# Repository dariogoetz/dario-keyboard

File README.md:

# Ergonomic Split and Unibody 42-key Keyboards

Split and unibody variants of an ergonomic (column staggered) 42-key keyboard inspired by the [Cantor](https://github.com/diepala/cantor) keyboard and designed using [ergogen](https://github.com/ergogen/ergogen).

It uses a firmware based on [keyberon](https://github.com/TeXitoi/keyberon).

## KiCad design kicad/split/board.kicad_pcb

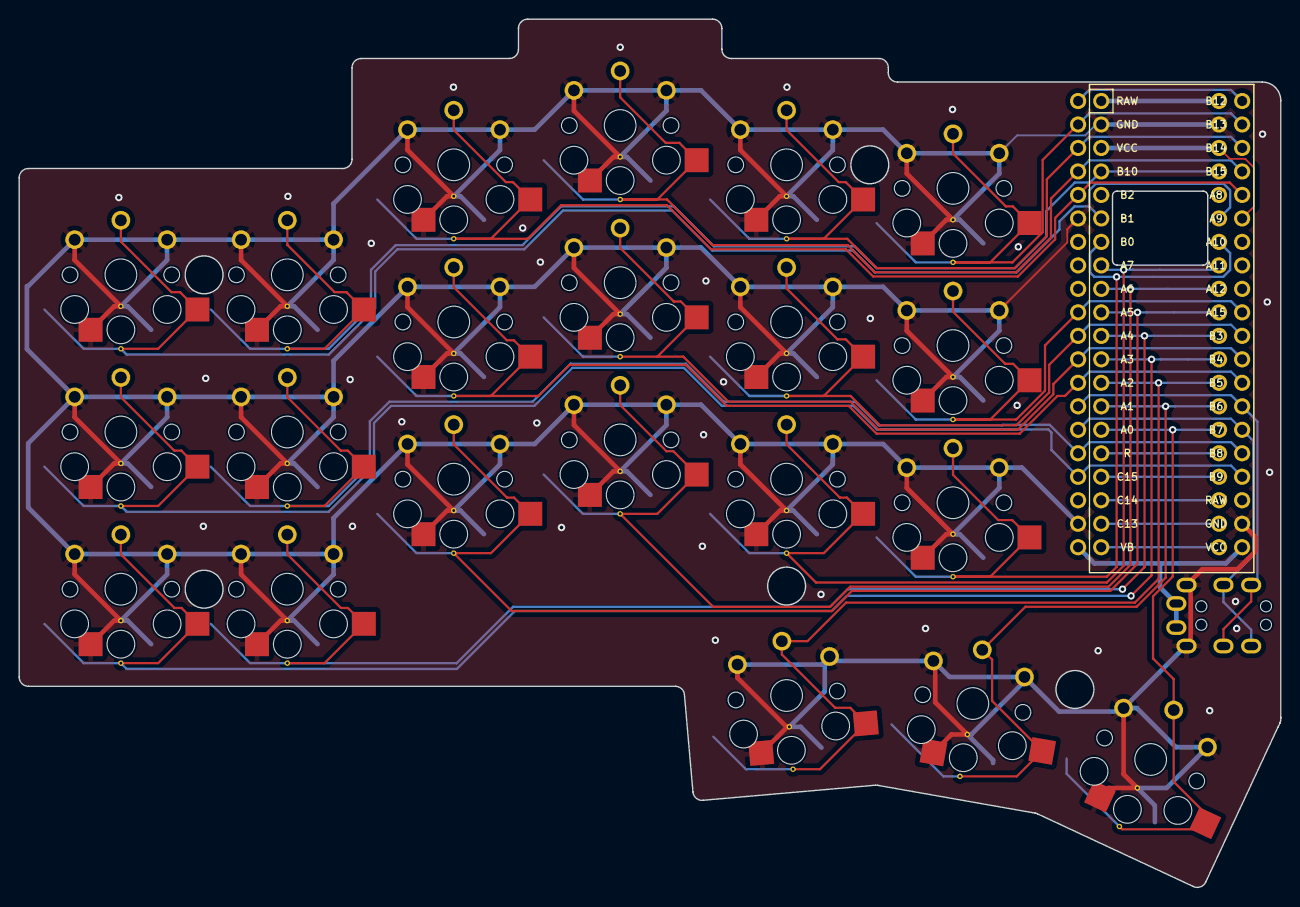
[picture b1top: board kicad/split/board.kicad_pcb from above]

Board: 2 copper layers, 136.5 x 93.9 mm, 25 parts (0 on the bottom side), 36 nets.

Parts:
MCU1, MCU2: Blackpill
S1, S2, S3, S4, S5, S6, S7, S8, S9, S10, S11, S12, S13, S14, S15, S16, S17, S18, S19, S20, S21: PG1350
TRRS1, TRRS2: TRRS-PJ-320A-dual

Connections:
A0: MCU1.15, MCU2.15, S21.2
A1: MCU1.14, MCU2.14, S20.2
A2: MCU1.13, MCU2.13, S19.2
A3: MCU1.12, MCU2.12, S1.2
A4: MCU1.11, MCU2.11, S4.2
A5: MCU1.10, MCU2.10, S7.2
A6: MCU1.9, MCU2.9, S10.2
A7: MCU1.8, MCU2.8, S13.2
A8: MCU1.25, MCU2.25, S9.2
A10: MCU1.27, MCU2.27
A11: MCU1.28, MCU2.28
A12: MCU1.29, MCU2.29
A15: MCU1.30, MCU2.30, S17.2
B0: MCU1.7, MCU2.7, S16.2
B1: MCU1.6, MCU2.6, S3.2
B2: MCU1.5, MCU2.5
B3: MCU1.31, MCU2.31, S14.2
B4: MCU1.32, MCU2.32, S11.2
B5: MCU1.33, MCU2.33, S8.2
B6: MCU1.34, MCU2.34, TRRS1.3, TRRS2.4
B7: MCU1.35, MCU2.35, TRRS1.4, TRRS2.3
B8: MCU1.36, MCU2.36, S5.2
B9: MCU1.37, MCU2.37, S2.2
B10: MCU1.4, MCU2.4, S6.2
B12: MCU1.21, MCU2.21
B13: MCU1.22, MCU2.22, S18.2
B14: MCU1.23, MCU2.23, S15.2
B15: MCU1.24, MCU2.24, S12.2
C13: MCU1.19, MCU2.19
C14: MCU1.18, MCU2.18
C15: MCU1.17, MCU2.17
GND: MCU1.2, MCU1.39, MCU2.2, MCU2.26, MCU2.39, S1.1, S2.1, S3.1, S4.1, S5.1, S6.1, S7.1, S8.1, S9.1, S10.1, S11.1, S12.1, S13.1, S14.1, S15.1, S16.1, S17.1, S18.1, S19.1, S20.1, S21.1, TRRS1.2, TRRS2.2
R: MCU1.16, MCU2.16
RAW: MCU1.1, MCU1.38, MCU2.1, MCU2.38
VB: MCU1.20, MCU2.20
VCC: MCU1.3, MCU1.26, MCU1.40, MCU2.3, MCU2.40, TRRS1.1, TRRS2.1

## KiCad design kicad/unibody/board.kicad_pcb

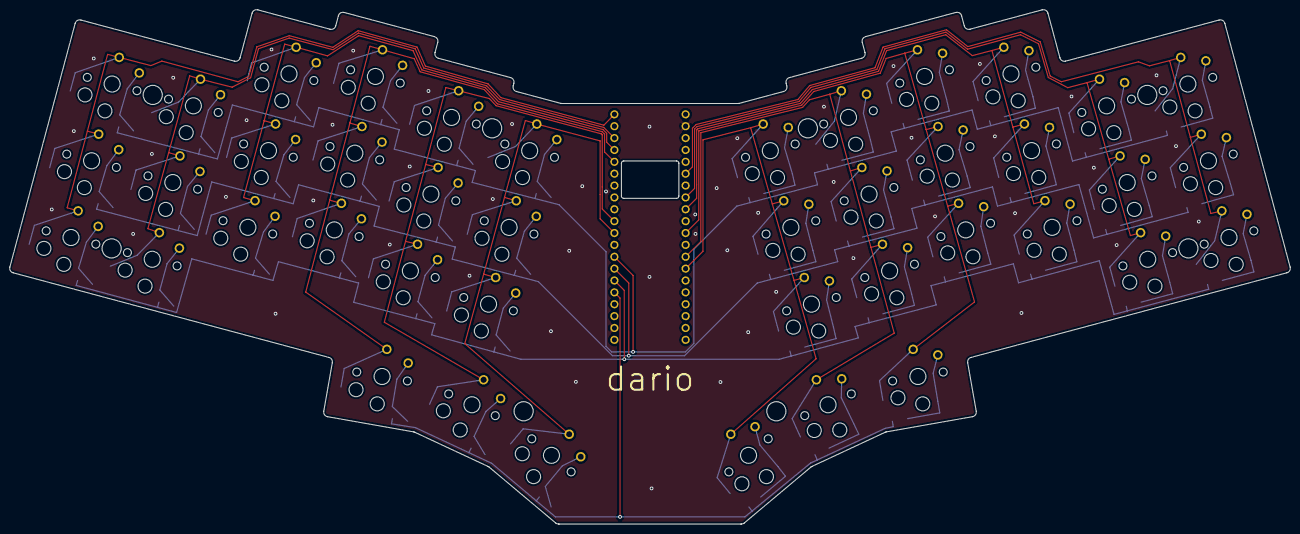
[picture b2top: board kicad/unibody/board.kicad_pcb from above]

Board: 2 copper layers, 274.0 x 110.1 mm, 85 parts (0 on the bottom side), 61 nets.

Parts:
D1, D2, D3, D4, D5, D6, D7, D8, D9, D10, D11, D12, D13, D14, D15, D16, D17, D18, D19, D20, D21, D22, D23, D24, D25, D26, D27, D28, D29, D30, D31, D32, D33, D34, D35, D36, D37, D38, D39, D40, D41, D42: ComboDiode
MCU1: Blackpill
S1, S2, S3, S4, S5, S6, S7, S8, S9, S10, S11, S12, S13, S14, S15, S16, S17, S18, S19, S20, S21, S22, S23, S24, S25, S26, S27, S28, S29, S30, S31, S32, S33, S34, S35, S36, S37, S38, S39, S40, S41, S42: PG1350

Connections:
A1: MCU1.14, S37.2, S38.2, S39.2, S42.2
A2: MCU1.13, S34.2, S35.2, S36.2, S41.2
A4: MCU1.11, S31.2, S32.2, S33.2, S40.2
A6: MCU1.9, S28.2, S29.2, S30.2
A7: MCU1.8, S25.2, S26.2, S27.2
A8: MCU1.25, S10.2, S11.2, S12.2, S19.2
A15: MCU1.30, S13.2, S14.2, S15.2, S20.2
B1: MCU1.6, S22.2, S23.2, S24.2
B3: MCU1.31, S16.2, S17.2, S18.2, S21.2
B5: D3.1, D6.1, D9.1, D12.1, D15.1, D18.1, D24.1, D27.1, D30.1, D33.1, D36.1, D39.1, MCU1.33
B6: D2.1, D5.1, D8.1, D11.1, D14.1, D17.1, D23.1, D26.1, D29.1, D32.1, D35.1, D38.1, MCU1.34
B7: D1.1, D4.1, D7.1, D10.1, D13.1, D16.1, D22.1, D25.1, D28.1, D31.1, D34.1, D37.1, MCU1.35
B8: D19.1, D20.1, D21.1, D40.1, D41.1, D42.1, MCU1.36
B12: MCU1.21, S1.2, S2.2, S3.2
B14: MCU1.23, S4.2, S5.2, S6.2
B15: MCU1.24, S7.2, S8.2, S9.2
GND: MCU1.2, MCU1.39
RAW: MCU1.1, MCU1.38
VCC: MCU1.3, MCU1.40
center_thumb: D20.2, S20.1
index_bottom: D13.2, S13.1
index_home: D14.2, S14.1
index_top: D15.2, S15.1
inner_bottom: D16.2, S16.1
inner_home: D17.2, S17.1
inner_thumb: D19.2, S19.1
inner_top: D18.2, S18.1
middle_bottom: D10.2, S10.1
middle_home: D11.2, S11.1
middle_top: D12.2, S12.1
mirror_center_thumb: D41.2, S41.1
mirror_index_bottom: D34.2, S34.1
mirror_index_home: D35.2, S35.1
mirror_index_top: D36.2, S36.1
mirror_inner_bottom: D37.2, S37.1
mirror_inner_home: D38.2, S38.1
mirror_inner_thumb: D40.2, S40.1
mirror_inner_top: D39.2, S39.1
mirror_middle_bottom: D31.2, S31.1
mirror_middle_home: D32.2, S32.1
mirror_middle_top: D33.2, S33.1
mirror_outer_bottom: D22.2, S22.1
mirror_outer_home: D23.2, S23.1
mirror_outer_thumb: D42.2, S42.1
mirror_outer_top: D24.2, S24.1
mirror_pinky_bottom: D25.2, S25.1
mirror_pinky_home: D26.2, S26.1
mirror_pinky_top: D27.2, S27.1
mirror_ring_bottom: D28.2, S28.1
mirror_ring_home: D29.2, S29.1
mirror_ring_top: D30.2, S30.1
outer_bottom: D1.2, S1.1
outer_home: D2.2, S2.1
outer_thumb: D21.2, S21.1
outer_top: D3.2, S3.1
pinky_bottom: D4.2, S4.1
pinky_home: D5.2, S5.1
pinky_top: D6.2, S6.1
ring_bottom: D7.2, S7.1
ring_home: D8.2, S8.1
ring_top: D9.2, S9.1

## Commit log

2023-02-09 [add] picture
2023-08-20 add: routed pcbs
2023-11-06 [mod] update keyberon for tri-state layers
2023-11-06 [add] cargo.lock
2023-11-06 [mod] use tri-state layers
2023-11-27 mod: update tri-layer syntax following keyberon changes
2023-12-01 add: .cargo/config.toml
2023-12-01 mod: update stm32 package hal
2024-07-09 feat: nkro
2024-08-11 feat: qwertz instead of noted layout
2025-10-09 fix(unibody): qwertz layout has 2 layers
2025-10-09 fix(build): use probe-rs instead of probe-run
